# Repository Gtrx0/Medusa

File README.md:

# Medusa

# [Layout](http://www.keyboard-layout-editor.com/##@@_a:7%3B&=&=&=&=&=&=&=%3B&@=&=&=&=&=&=&=%3B&@=&=&=&=&=&=&=%3B&@=&=&=&=&=&=&=%3B&@=&=&=&=&=&=&=)

## Features
* Compatible with Cherry MX and ALPS switches.
* Wireless Bluetooth operation.
* Bluetooth achieved by nrf51822 chip and receiver with an pro mico
* 2 CR2023 coin cell batteries for long battery life. 
* Estimated 10 month continuous battery life
* Switch to turn off batteries when the keyboard is not in use.
* 5x7 ortholinear layout with 2 break-away columns and 1 break-away row.
* SMD diodes for ease of assembly
* Mosfet reverse current protection
* Programming header on the side of the PCB.

## Warning
KiCad 5 or above is needed to open this project. KiCad 4 or below won't work.

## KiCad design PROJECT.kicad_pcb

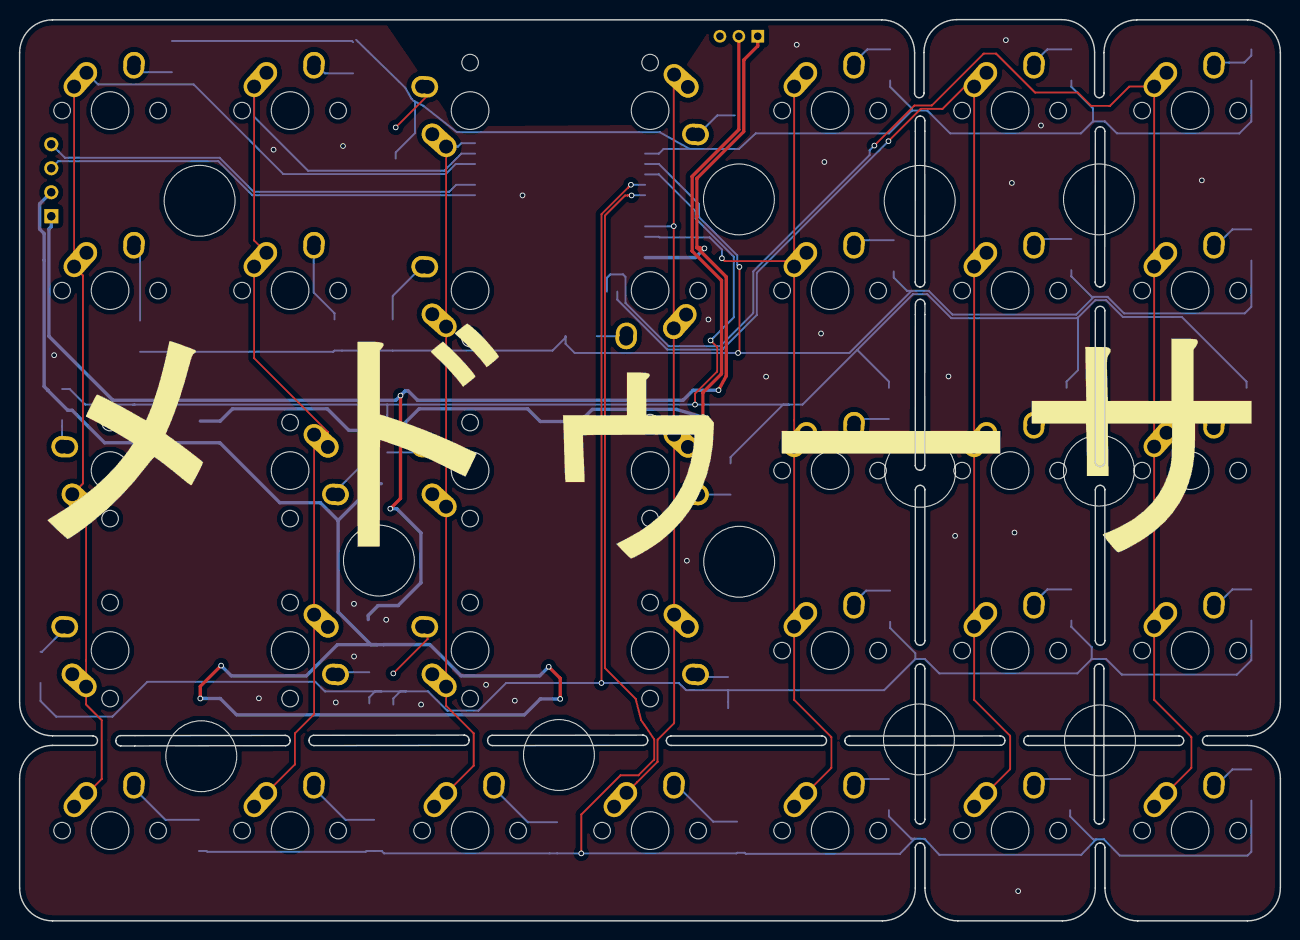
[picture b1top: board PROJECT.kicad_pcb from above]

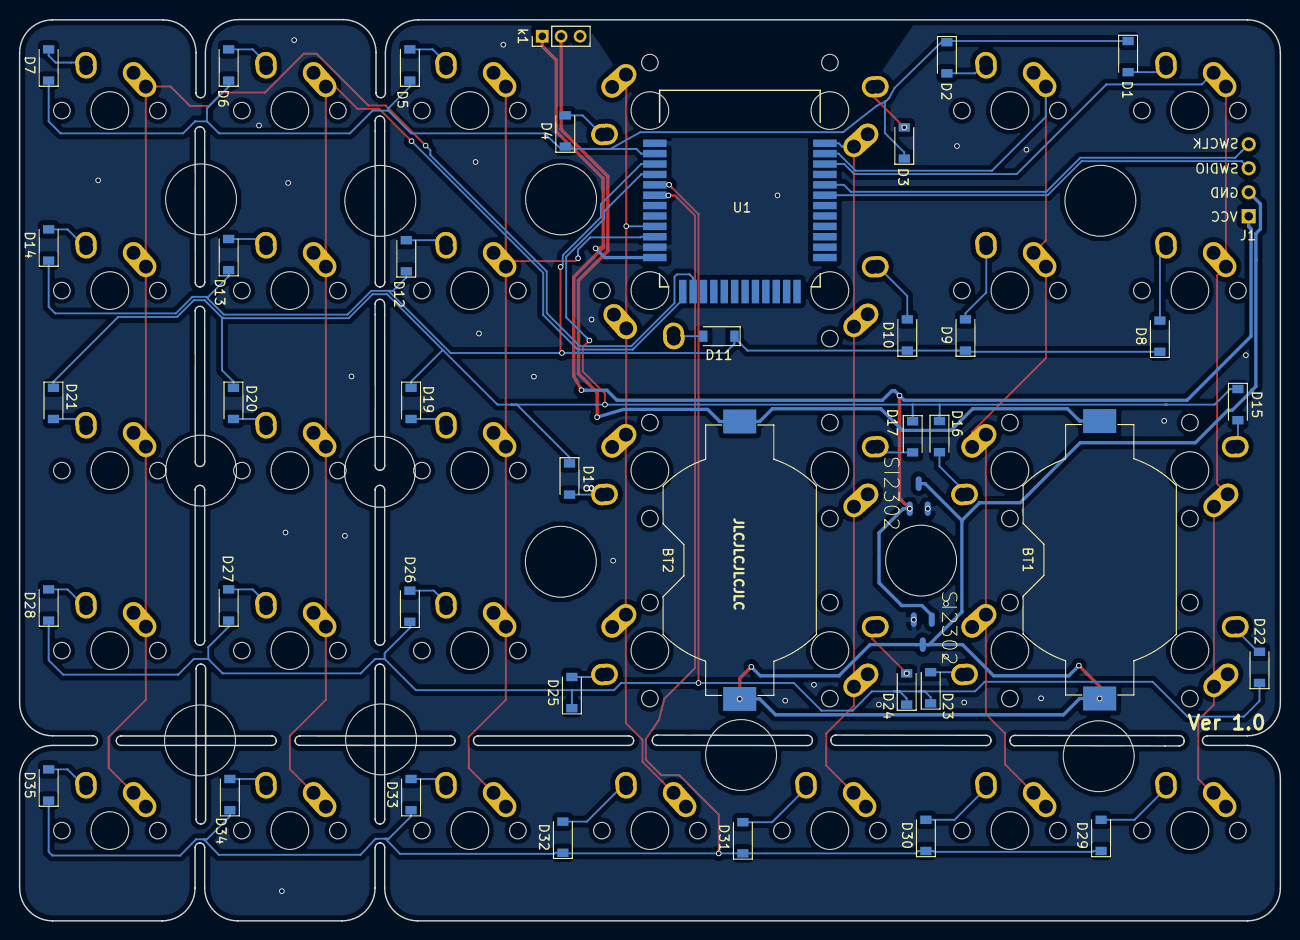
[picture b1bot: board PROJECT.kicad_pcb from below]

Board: 2 copper layers, 133.4 x 95.4 mm, 89 parts (42 on the bottom side), 53 nets.

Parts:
BT1, BT2: Battery_Cell; Keystone_1058_1x2032-CoinCell
D1, D2, D3, D4, D5, D6, D7, D8, D9, D10, D11, D12, D13, D14, D15, D16, D17, D18, D19, D20, D21, D22, D23, D24, D25, D26, D27, D28, D29, D30, D31, D32, D33, D34, D35: D_ALT; D_SOD-123
J1: Conn_01x04; programming_port
MX1, MX2, MX3, MX4, MX5, MX6, MX7, MX8, MX9, MX10, MX11, MX12, MX13, MX14, MX15, MX16, MX17, MX18, MX19, MX20, MX21, MX22, MX23, MX24, MX25, MX26, MX27, MX28, MX29, MX30, MX31, MX32, MX33, MX34, MX35: MX-1U; MX-1U-NoLED
P?: CONN_1; PIN_1
P?#2, P?#3, P?#4, P?#5, P?#6, P?#7, P?#8, P?#9, P?#10, P?#11, P?#12: CONN_1; PIN_1
Q1, Q2: SI2302; SI3202CDS
U1: Core51822B; Core51822(B)
k1: KEYSW; Pin_Header_Straight_1x03_Pitch2.00mm

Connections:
COL0: MX1.1, MX8.1, MX15.1, MX22.1, MX29.1, U1.34
COL1: MX2.1, MX9.1, MX16.1, MX23.1, MX30.1, U1.35
COL2: MX3.1, MX10.1, MX17.1, MX24.1, MX31.1, U1.36
COL3: MX4.1, MX11.1, MX18.1, MX25.1, MX32.1, U1.9
COL4: MX5.1, MX12.1, MX19.1, MX26.1, MX33.1, U1.10
COL5: MX6.1, MX13.1, MX20.1, MX27.1, MX34.1, U1.13
COL6: MX7.1, MX14.1, MX21.1, MX28.1, MX35.1, U1.14
GND: Q1.2, Q2.2, U1.1, U1.11
GND_BAT: BT1.2, BT2.2, J1.2, Q1.3, Q2.3
unnamed: D1.2, MX1.2
unnamed: D2.2, MX2.2
unnamed: D3.2, MX3.2
unnamed: D4.2, MX4.2
unnamed: D5.2, MX5.2
unnamed: D6.2, MX6.2
unnamed: D7.2, MX7.2
unnamed: D8.2, MX8.2
unnamed: D9.2, MX9.2
unnamed: D10.2, MX10.2
unnamed: D11.2, MX11.2
unnamed: D12.2, MX12.2
unnamed: D13.2, MX13.2
unnamed: D14.2, MX14.2
unnamed: D15.2, MX15.2
unnamed: D16.2, MX16.2
unnamed: D17.2, MX17.2
unnamed: D18.2, MX18.2
unnamed: D19.2, MX19.2
unnamed: D20.2, MX20.2
unnamed: D21.2, MX21.2
unnamed: D22.2, MX22.2
unnamed: D23.2, MX23.2
unnamed: D24.2, MX24.2
unnamed: D25.2, MX25.2
unnamed: D26.2, MX26.2
unnamed: D27.2, MX27.2
unnamed: D28.2, MX28.2
unnamed: D29.2, MX29.2
unnamed: D30.2, MX30.2
unnamed: D31.2, MX31.2
unnamed: D32.2, MX32.2
unnamed: D33.2, MX33.2
unnamed: D34.2, MX34.2
unnamed: D35.2, MX35.2
ROW0: D1.1, D2.1, D3.1, D4.1, D5.1, D6.1, D7.1, U1.2
ROW1: D8.1, D9.1, D10.1, D11.1, D12.1, D13.1, D14.1, U1.3
ROW2: D15.1, D16.1, D17.1, D18.1, D19.1, D20.1, D21.1, U1.4
ROW3: D22.1, D23.1, D24.1, D25.1, D26.1, D27.1, D28.1, U1.5
ROW4: D29.1, D30.1, D31.1, D32.1, D33.1, D34.1, D35.1, U1.6
SWCLK: J1.4, U1.32
SWDIO: J1.3, U1.31
VCC: J1.1, Q1.1, Q2.1, U1.12, k1.1
VCC_S: BT1.1, BT2.1, k1.2

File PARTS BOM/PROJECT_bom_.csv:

Component,Description,Part,References,Value,Footprint,Quantity Per PCB,Datasheet
1,Cr 2023 Holder Keystone 1058,Battery_Cell,BT1 BT2,Battery_Cell,Keystone_1058_1x2032-CoinCell,2,~
2,SMD diode,D_ALT,D1 D2 D3 D4 D5 D6 D7 D8 D9 D10 D11 D12 D13 D14 D15 D16 D17 D18 D19 D20 D21 D22 D23 D24 D25 D26 D27 D28 D29 D30 D31 D32 D33 D34 D35,D_ALT,D_SOD-123,35,~
3,"Generic connector, single row, 01x04",Conn_01x04,J1,Conn_01x04,programming_port,1,~
4,N channel mosfet,SI2302,Q1 Q2,SI2302,SI3202CDS,2,
5,nrf51822B Breakout Board,Core51822B,U1,Core51822B,Core51822(B),1,
6,Slide Switch,KEYSW,k1,KEYSW,SW_DIP_x1_W7.62mm_Slide,1,
,,,,,,,
,,,,,,,
,,,,,,,
,,,,,,,
,,,,,,,
Component Groups:,7,,,,,,
Component Count:,42,,,,,,
Fitted Components:,42,,,,,,
Number of PCBs:,1,,,,,,
Total components:,42,,,,,,
Schematic Version:,,,,,,,
Schematic Date:,,,,,,,
BoM Date:,9/7/2018 7:01:59 PM,,,,,,
Schematic Source:,C:\Users\Gtrx\Documents\GitHub\Medusa\PROJECT.sch,,,,,,
KiCad Version:,Eeschema (5.0.0),,,,,,

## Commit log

2018-09-01 Medusa
2018-09-02 Re-routed
2018-09-07 Deleted Files
2018-09-07 Added BOM
2018-09-15 routing
2018-09-22 Plate design
